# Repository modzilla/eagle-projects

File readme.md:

# My Eagle Projects

## Attention: Most of them are junk!

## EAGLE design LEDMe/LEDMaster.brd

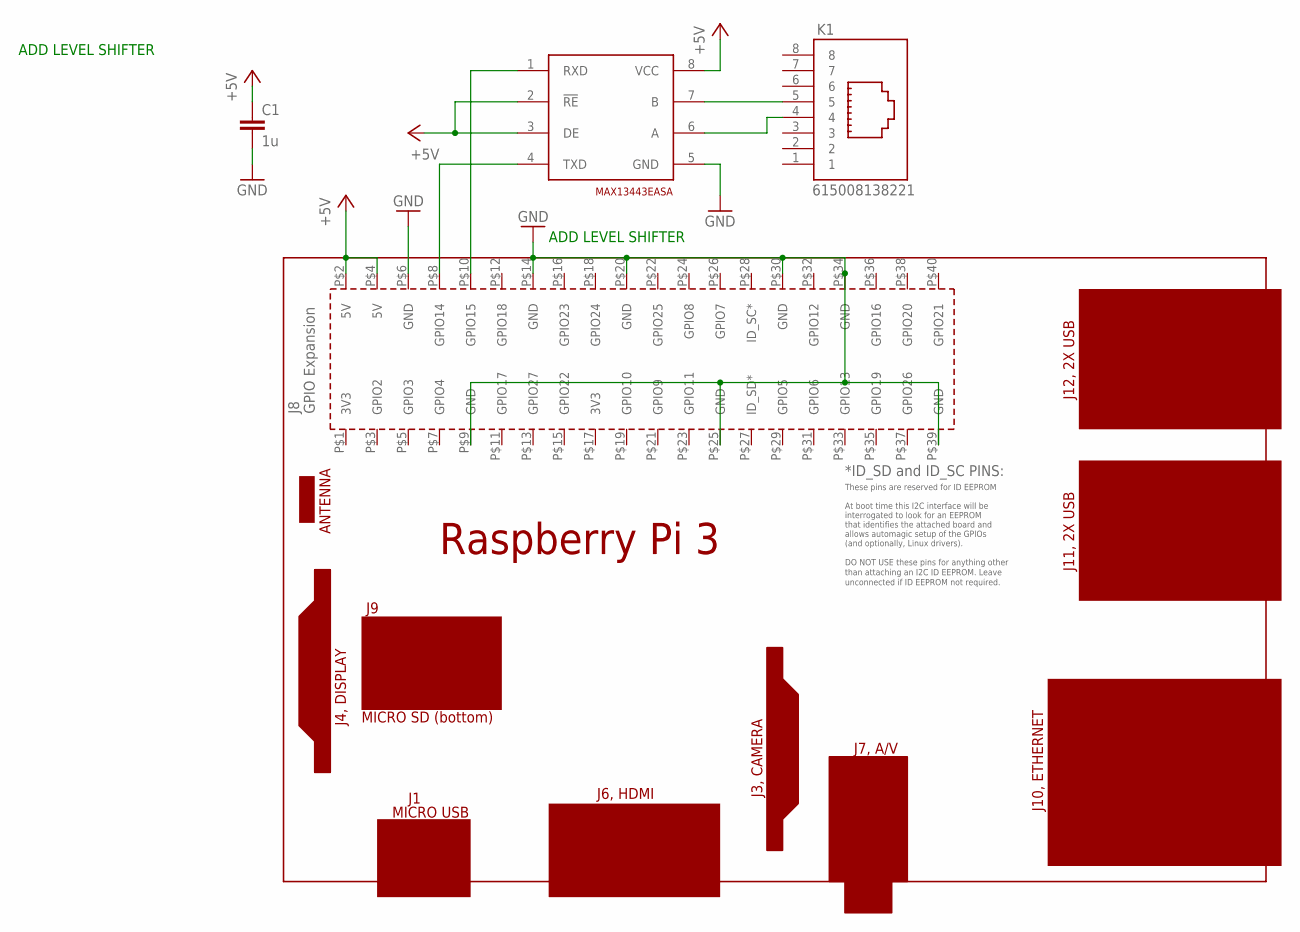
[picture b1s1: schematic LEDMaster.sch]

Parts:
C1: 1u; C1206
K1: 615008138221
PCB1: RPI3
U$1: MAX13443EASA; SO08

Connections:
+5V: C1.1, PCB1.P$2 (5V), PCB1.P$4 (5V), U$1.2 (!RE), U$1.3 (DE), U$1.8 (VCC)
GND: C1.2, PCB1.P$6 (GND), PCB1.P$9 (GND), PCB1.P$14 (GND), PCB1.P$20 (GND), PCB1.P$25 (GND), PCB1.P$30 (GND), PCB1.P$34 (GND), PCB1.P$39 (GND), U$1.5 (GND)
unnamed: PCB1.P$8 (GPIO14), U$1.4 (TXD)
unnamed: PCB1.P$10 (GPIO15), U$1.1 (RXD)
unnamed: K1.5, U$1.7 (B)
unnamed: K1.4, U$1.6 (A)

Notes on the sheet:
ADD LEVEL SHIFTER

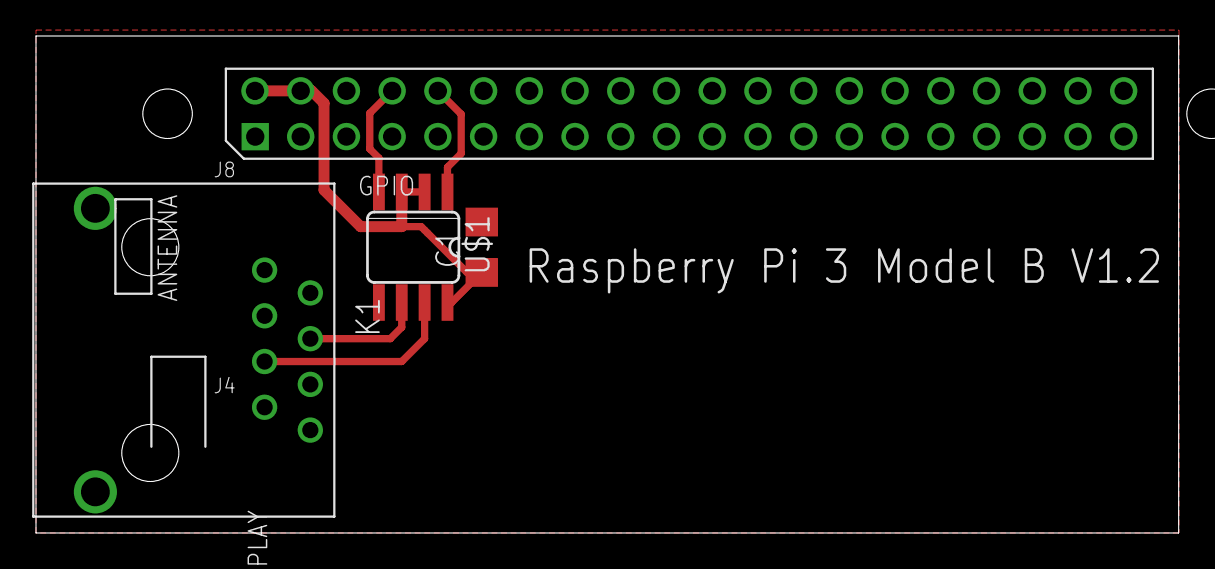
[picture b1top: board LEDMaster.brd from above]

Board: 2 copper layers, 63.5 x 27.6 mm, 4 parts (0 on the bottom side), 6 nets.

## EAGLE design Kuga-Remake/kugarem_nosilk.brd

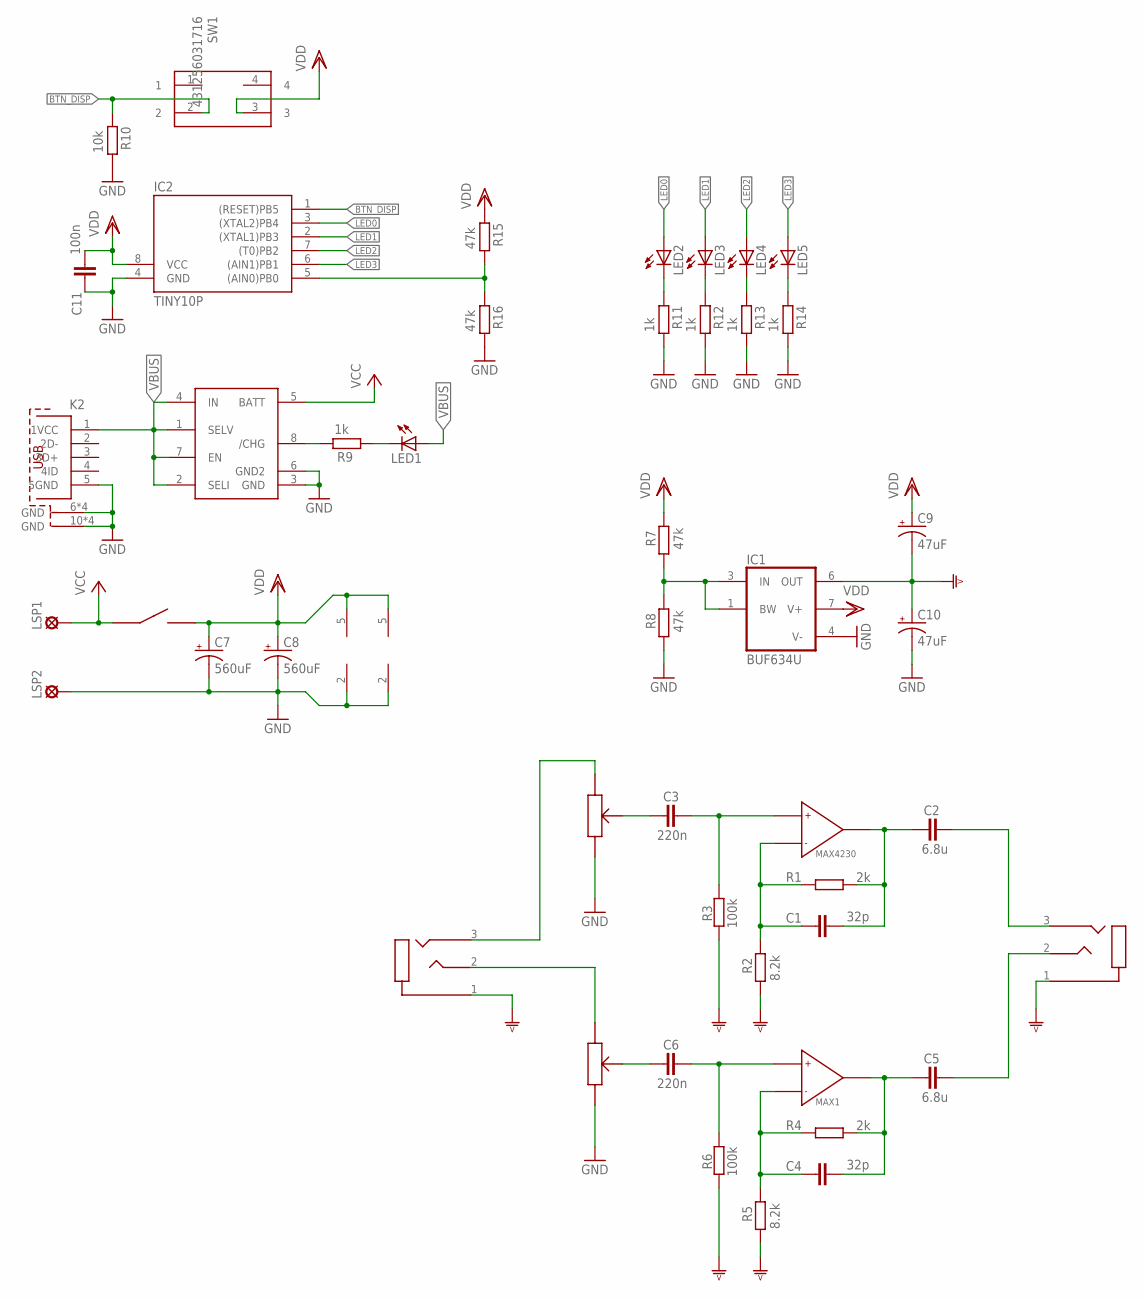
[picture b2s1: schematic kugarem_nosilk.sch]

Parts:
C1, C4: 32p; C1206
C2, C5: 6.8u; C1206
C3, C6: 220n; C1206
C7, C8: 560uF; PANASONIC_G
C9, C10: 47uF; PANASONIC_D
C11: 100n; C1206
IC1: BUF634U; SO08
IC2: TINY10P; DIL08
K2: 629105150921
LED1, LED2, LED3, LED4, LED5: LEDCHIPLED_1206; CHIPLED_1206
LSP1, LSP2: LSP10
MAX1, MAX4230: MAX4230; SOT23-5L
R1, R4: 2k; R1206
R2, R5: 8.2k; R1206
R3, R6: 100k; R1206
R7, R8, R15, R16: 47k; R1206
R9, R11, R12, R13, R14: 1k; R1206
R10: 10k; R1206
SW1: 431256031716
U$1: 100k; PTR902
U$2, U$3: SJ1-3515-SMT-TR; STX-35332-3N-TR
U$4: MAX1811SO8; SO08

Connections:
BTN_DISP: IC2.1 ((RESET)PB5), R10.2, SW1.2
GND: C7.-, C8.-, C10.-, C11.1, IC1.4 (V-), IC2.4 (GND), K2.5 (5GND), K2.6 (GND), K2.7 (GND), K2.8 (GND), K2.9 (GND), K2.10 (GND), K2.11 (GND), K2.12 (GND), K2.13 (GND), LSP2.MP, MAX1.2 (N), MAX4230.2 (N), R8.2, R10.1, R11.1, R12.1, R13.1, R14.1, R16.1, U$1.R13 (13), U$1.R23 (13), U$4.3 (GND), U$4.6 (GND2)
LED0: IC2.3 ((XTAL2)PB4), LED2.A
LED1: IC2.2 ((XTAL1)PB3), LED3.A
LED2: IC2.7 ((T0)PB2), LED4.A
LED3: IC2.6 ((AIN1)PB1), LED5.A
unnamed: C1.2, C2.1, MAX4230.4 (OUT), R1.1
unnamed: C1.1, MAX4230.3 (IN-), R1.2, R2.1
unnamed: C2.2, U$3.3 (RING)
unnamed: C3.2, MAX4230.1 (IN+), R3.1
unnamed: C4.2, C5.1, MAX1.4 (OUT), R4.1
unnamed: C4.1, MAX1.3 (IN-), R4.2, R5.1
unnamed: C3.1, U$1.R22 (12)
unnamed: C6.2, MAX1.1 (IN+), R6.1
unnamed: C5.2, U$3.2 (TIP)
unnamed: C6.1, U$1.R12 (12)
unnamed: U$1.R21 (11), U$2.3 (RING)
unnamed: U$1.R11 (11), U$2.2 (TIP)
unnamed: LED2.C, R11.2
unnamed: LED3.C, R12.2
unnamed: LED1.C, R9.2
unnamed: R9.1, U$4.8 (/CHG)
unnamed: IC1.1 (BW), IC1.3 (IN), R7.2, R8.1
unnamed: LED4.C, R13.2
unnamed: LED5.C, R14.2
unnamed: IC2.5 ((AIN0)PB0), R15.1, R16.2
VBUS: K2.1 (1VCC), LED1.A, U$4.1 (SELV), U$4.2 (SELI), U$4.4 (IN), U$4.7 (EN)
VCC: LSP1.MP, U$1.SW1 (11), U$4.5 (BATT)
VDD: C7.+, C8.+, C9.+, C11.2, IC1.7 (V+), IC2.8 (VCC), MAX1.5, MAX4230.5, R7.1, R15.2, SW1.3, U$1.SW2 (12)
VGND: C9.-, C10.+, IC1.6 (OUT), R2.2, R3.2, R5.2, R6.2, U$2.1 (SLEEVE), U$3.1 (SLEEVE)

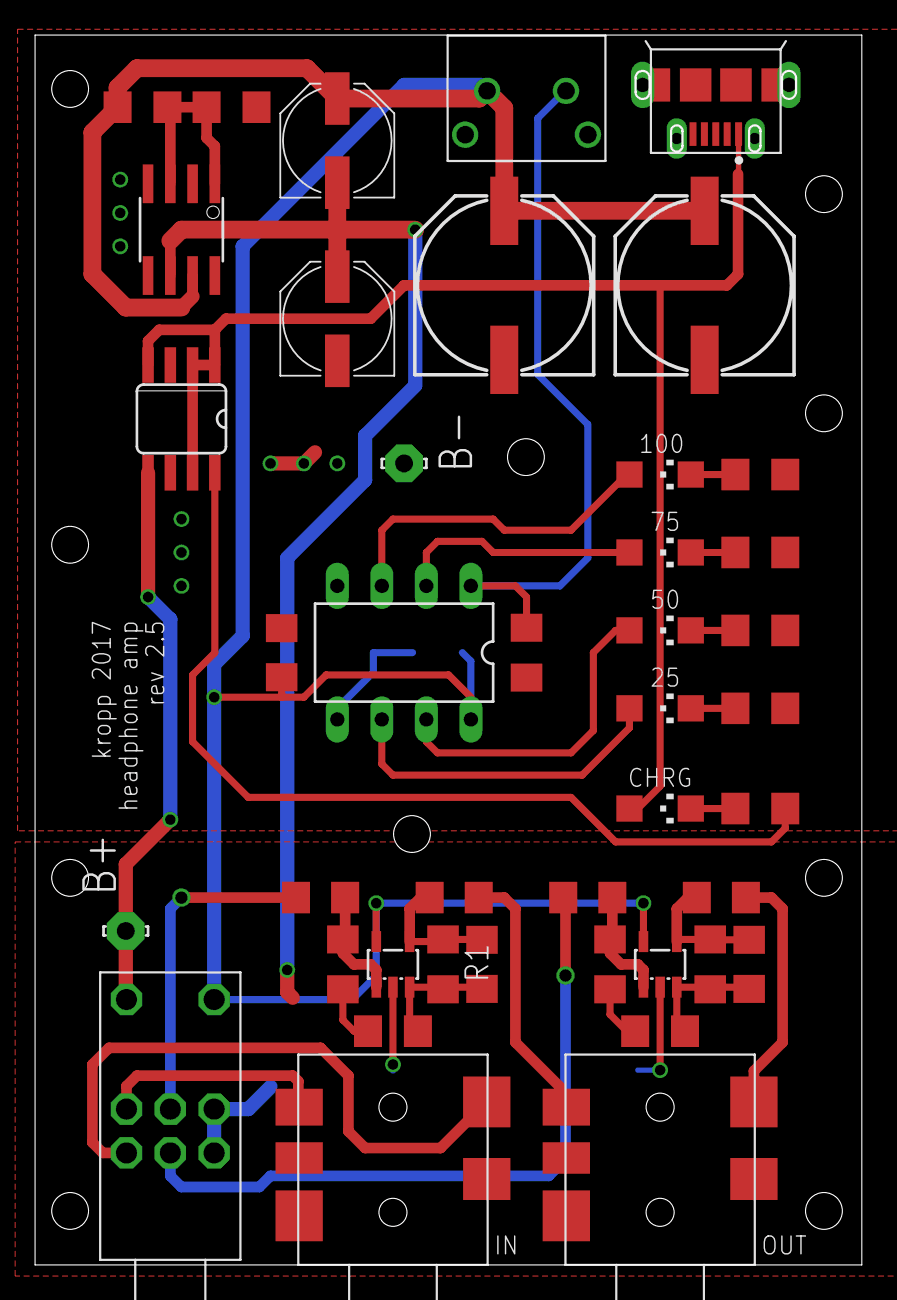
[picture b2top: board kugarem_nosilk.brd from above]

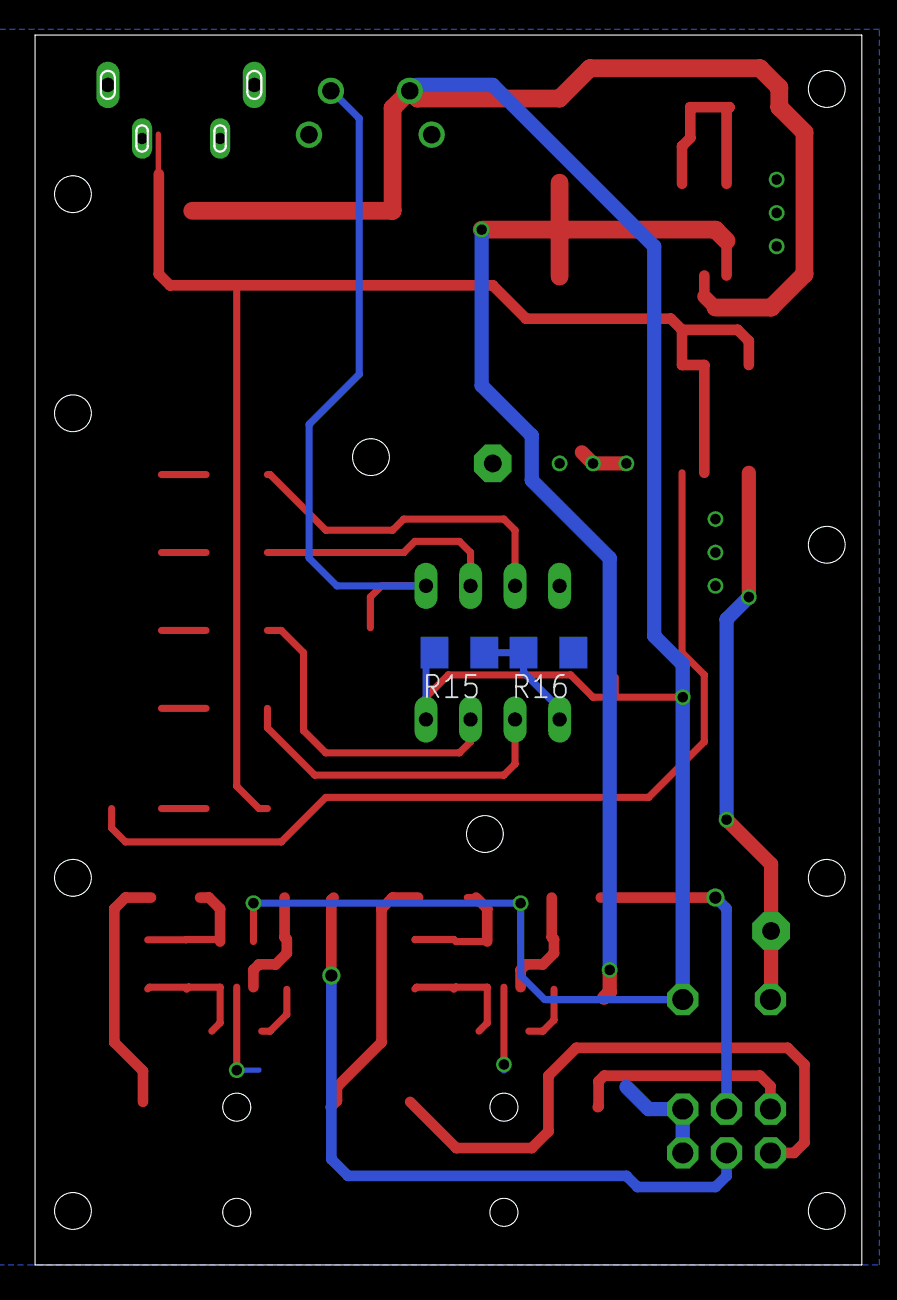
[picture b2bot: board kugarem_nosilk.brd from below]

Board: 2 copper layers, 47.2 x 70.2 mm, 44 parts (2 on the bottom side), 30 nets.

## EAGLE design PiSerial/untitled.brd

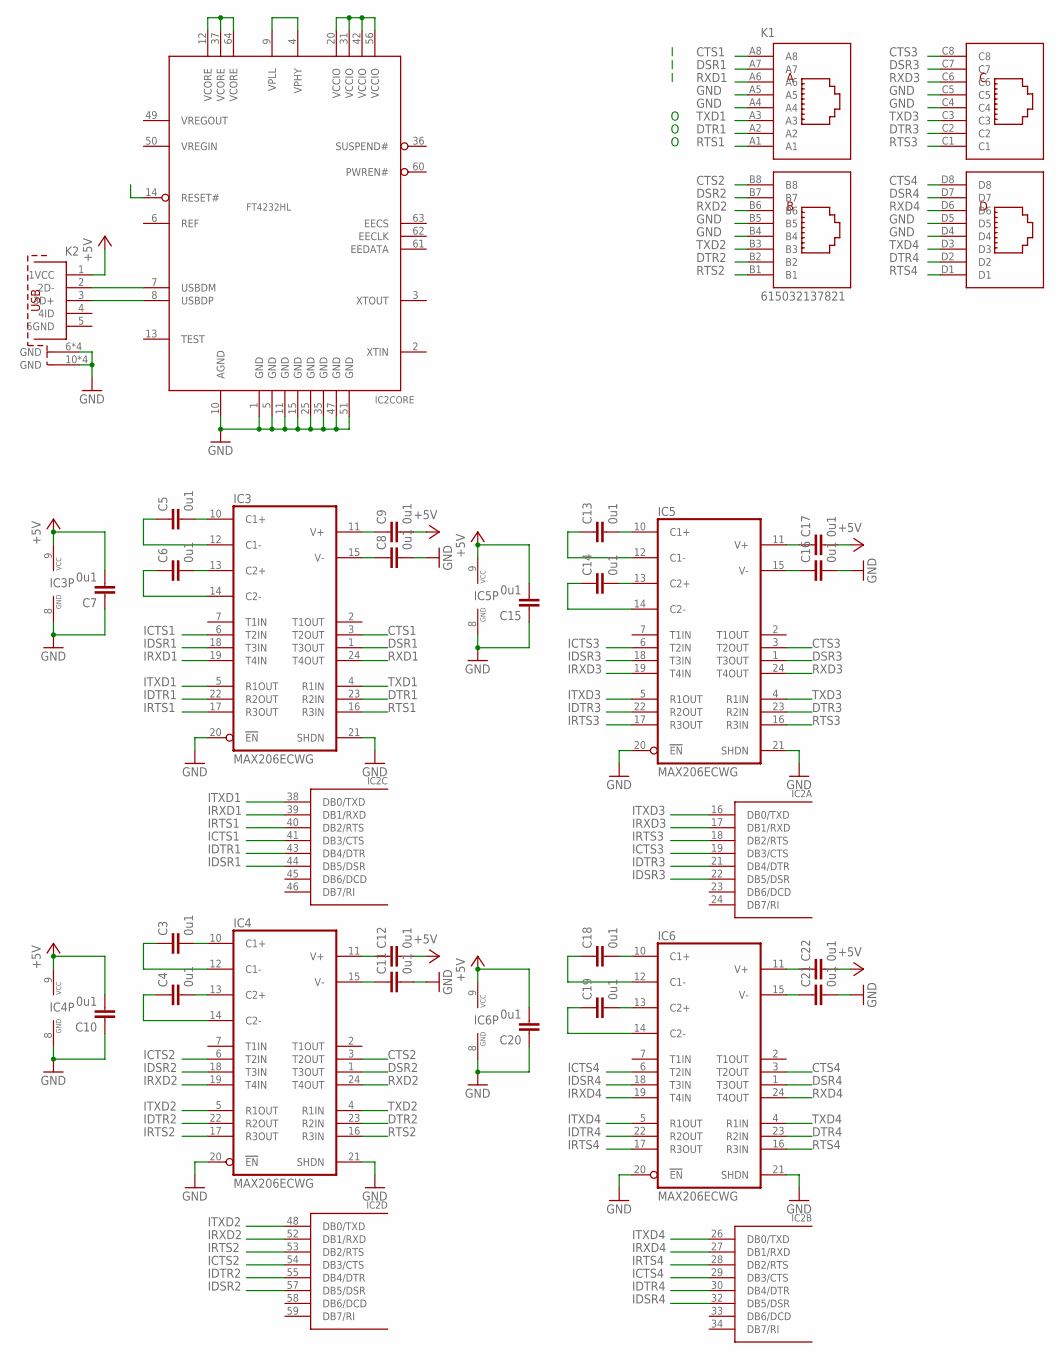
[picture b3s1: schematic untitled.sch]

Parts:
C3, C4, C5, C6, C7, C8, C9, C10, C11, C12, C13, C14, C15, C16, C17, C18, C19, C20, C21, C22: 0u1; C0603
IC2: FT4232HL; LQFP64
IC3, IC4, IC5, IC6: MAX206ECWG; SO24L
K1: 615032137821
K2: 629105150921

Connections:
+5V: C7.2, C9.2, C10.2, C12.2, C15.2, C17.2, C20.2, C22.2, IC3.9 (VCC), IC4.9 (VCC), IC5.9 (VCC), IC6.9 (VCC), K2.1 (1VCC)
CTS1: IC3.3 (T2OUT), K1.A8
CTS2: IC4.3 (T2OUT), K1.B8
CTS3: IC5.3 (T2OUT), K1.C8
CTS4: IC6.3 (T2OUT), K1.D8
DSR1: IC3.1 (T3OUT), K1.A7
DSR2: IC4.1 (T3OUT), K1.B7
DSR3: IC5.1 (T3OUT), K1.C7
DSR4: IC6.1 (T3OUT), K1.D7
DTR1: IC3.23 (R2IN), K1.A2
DTR2: IC4.23 (R2IN), K1.B2
DTR3: IC5.23 (R2IN), K1.C2
DTR4: IC6.23 (R2IN), K1.D2
GND: C7.1, C8.2, C10.1, C11.2, C15.1, C16.2, C20.1, C21.2, IC2.1 (GND), IC2.5 (GND), IC2.10 (AGND), IC2.11 (GND), IC2.15 (GND), IC2.25 (GND), IC2.35 (GND), IC2.47 (GND), IC2.51 (GND), IC3.8 (GND), IC3.20 (EN), IC3.21 (SHDN), IC4.8 (GND), IC4.20 (EN), IC4.21 (SHDN), IC5.8 (GND), IC5.20 (EN), IC5.21 (SHDN), IC6.8 (GND), IC6.20 (EN), IC6.21 (SHDN), K1.A4, K1.A5, K1.B4, K1.B5, K1.C4, K1.C5, K1.D4, K1.D5, K2.6 (GND), K2.7 (GND), K2.8 (GND), K2.9 (GND), K2.10 (GND), K2.11 (GND), K2.12 (GND), K2.13 (GND)
ICTS1: IC2.41 (DB3/CTS), IC3.6 (T2IN)
ICTS2: IC2.54 (DB3/CTS), IC4.6 (T2IN)
ICTS3: IC2.19 (DB3/CTS), IC5.6 (T2IN)
ICTS4: IC2.29 (DB3/CTS), IC6.6 (T2IN)
IDSR1: IC2.44 (DB5/DSR), IC3.18 (T3IN)
IDSR2: IC2.57 (DB5/DSR), IC4.18 (T3IN)
IDSR3: IC2.22 (DB5/DSR), IC5.18 (T3IN)
IDSR4: IC2.32 (DB5/DSR), IC6.18 (T3IN)
IDTR1: IC2.43 (DB4/DTR), IC3.22 (R2OUT)
IDTR2: IC2.55 (DB4/DTR), IC4.22 (R2OUT)
IDTR3: IC2.21 (DB4/DTR), IC5.22 (R2OUT)
IDTR4: IC2.30 (DB4/DTR), IC6.22 (R2OUT)
IRTS1: IC2.40 (DB2/RTS), IC3.17 (R3OUT)
IRTS2: IC2.53 (DB2/RTS), IC4.17 (R3OUT)
IRTS3: IC2.18 (DB2/RTS), IC5.17 (R3OUT)
IRTS4: IC2.28 (DB2/RTS), IC6.17 (R3OUT)
IRXD1: IC2.39 (DB1/RXD), IC3.19 (T4IN)
IRXD2: IC2.52 (DB1/RXD), IC4.19 (T4IN)
IRXD3: IC2.17 (DB1/RXD), IC5.19 (T4IN)
IRXD4: IC2.27 (DB1/RXD), IC6.19 (T4IN)
ITXD1: IC2.38 (DB0/TXD), IC3.5 (R1OUT)
ITXD2: IC2.48 (DB0/TXD), IC4.5 (R1OUT)
ITXD3: IC2.16 (DB0/TXD), IC5.5 (R1OUT)
ITXD4: IC2.26 (DB0/TXD), IC6.5 (R1OUT)
unnamed: C3.2, IC4.10 (C1+)
unnamed: C3.1, IC4.12 (C1-)
unnamed: IC2.20 (VCCIO), IC2.31 (VCCIO), IC2.42 (VCCIO), IC2.56 (VCCIO)
unnamed: IC2.4 (VPHY), IC2.9 (VPLL)
unnamed: C4.2, IC4.13 (C2+)
unnamed: C5.2, IC3.10 (C1+)
unnamed: C5.1, IC3.12 (C1-)
unnamed: C6.2, IC3.13 (C2+)
unnamed: C6.1, IC3.14 (C2-)
unnamed: C4.1, IC4.14 (C2-)
unnamed: C12.1, IC4.11 (V+)
unnamed: C9.1, IC3.11 (V+)
unnamed: C8.1, IC3.15 (V-)
unnamed: C11.1, IC4.15 (V-)
unnamed: C13.2, IC5.10 (C1+)
unnamed: C13.1, IC5.12 (C1-)
unnamed: C14.2, IC5.13 (C2+)
unnamed: C14.1, IC5.14 (C2-)
unnamed: C17.1, IC5.11 (V+)
unnamed: C16.1, IC5.15 (V-)
unnamed: C18.2, IC6.10 (C1+)
unnamed: C18.1, IC6.12 (C1-)
unnamed: C19.2, IC6.13 (C2+)
unnamed: C19.1, IC6.14 (C2-)
unnamed: C22.1, IC6.11 (V+)
unnamed: C21.1, IC6.15 (V-)
unnamed: IC2.12 (VCORE), IC2.37 (VCORE), IC2.64 (VCORE)
unnamed: IC2.8 (USBDP), K2.3 (3D+)
unnamed: IC2.7 (USBDM), K2.2 (2D-)
RTS1: IC3.16 (R3IN), K1.A1
RTS2: IC4.16 (R3IN), K1.B1
RTS3: IC5.16 (R3IN), K1.C1
RTS4: IC6.16 (R3IN), K1.D1
RXD1: IC3.24 (T4OUT), K1.A6
RXD2: IC4.24 (T4OUT), K1.B6
RXD3: IC5.24 (T4OUT), K1.C6
RXD4: IC6.24 (T4OUT), K1.D6
TXD1: IC3.4 (R1IN), K1.A3
TXD2: IC4.4 (R1IN), K1.B3
TXD3: IC5.4 (R1IN), K1.C3
TXD4: IC6.4 (R1IN), K1.D3

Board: 2 copper layers, 27 parts (0 on the bottom side), 79 nets, no tracks yet.

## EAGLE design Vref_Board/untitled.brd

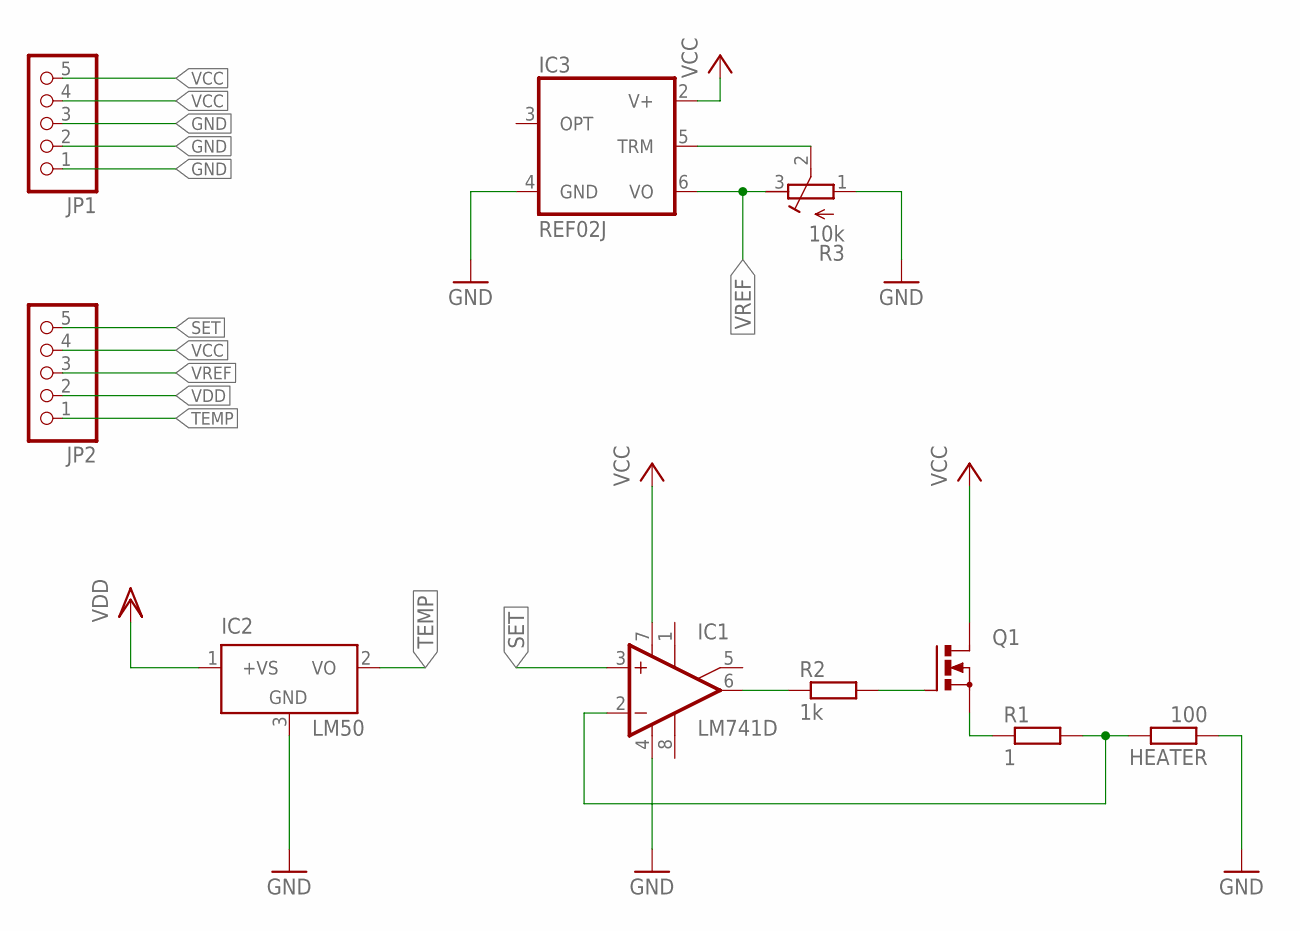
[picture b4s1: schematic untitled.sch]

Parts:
HEATER: 100; WSC0001
IC1: LM741D; SO08
IC2: LM50; SOT23
IC3: REF02J; TO99
JP1, JP2: PINHD-1X5; 1X05
Q1: N-MOSFET-SO8S; SO-08
R1: 1; R1206
R2: 1k; R1206
R3: 10k; RTRIM3103

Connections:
GND: HEATER.1, IC1.4 (V-), IC2.3 (GND), IC3.4 (GND), JP1.1, JP1.2, JP1.3, R3.1 (A)
unnamed: IC1.6 (OUT), R2.1
unnamed: Q1.4 (G), R2.2
unnamed: HEATER.2, IC1.2 (-IN), R1.2
unnamed: Q1.1 (S), Q1.2 (S), Q1.3 (S), R1.1
unnamed: IC3.5 (TRM), R3.2 (S)
SET: IC1.3 (+IN), JP2.5
TEMP: IC2.2 (VO), JP2.1
VCC: IC1.7 (V+), IC3.2 (V+), JP1.4, JP1.5, JP2.4, Q1.5 (D), Q1.6 (D), Q1.7 (D), Q1.8 (D)
VDD: IC2.1 (+VS), JP2.2
VREF: IC3.6 (VO), JP2.3, R3.3 (E)

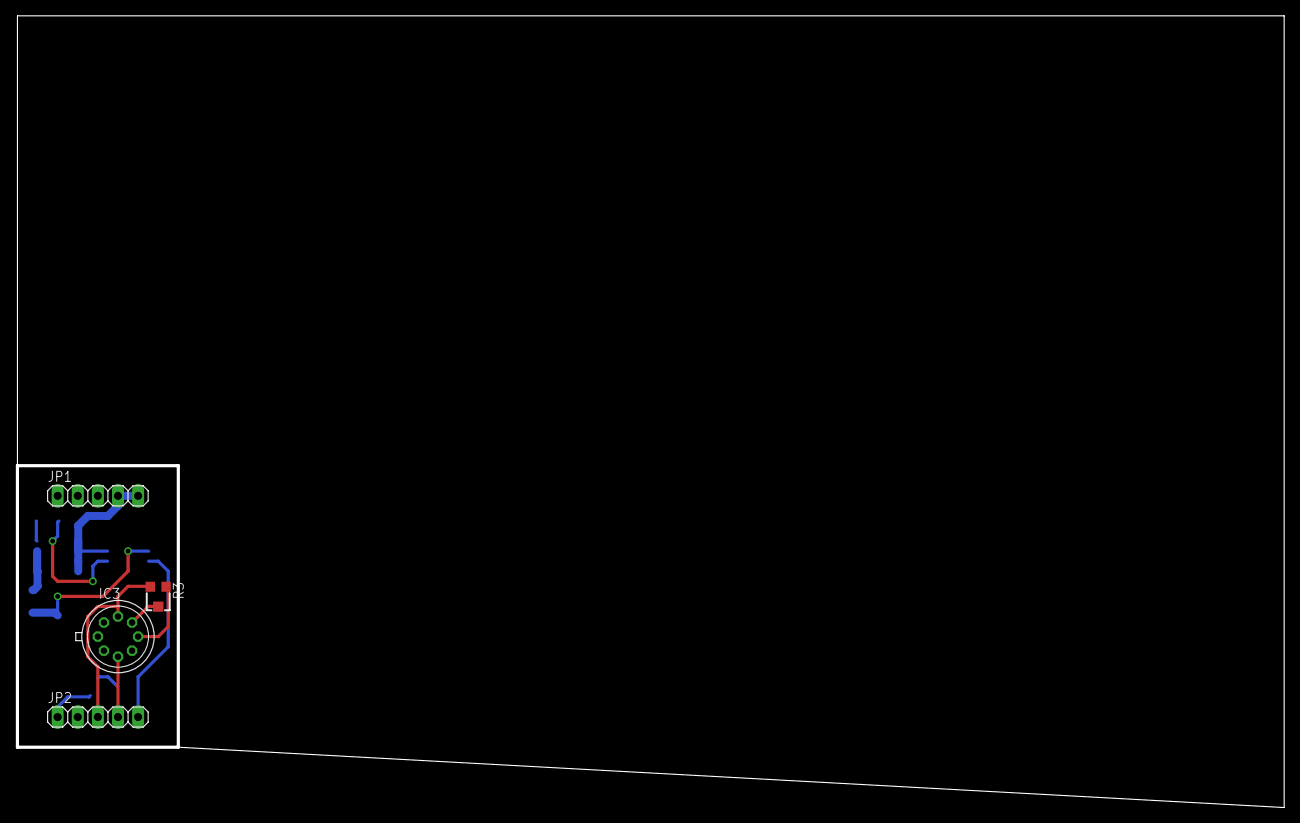
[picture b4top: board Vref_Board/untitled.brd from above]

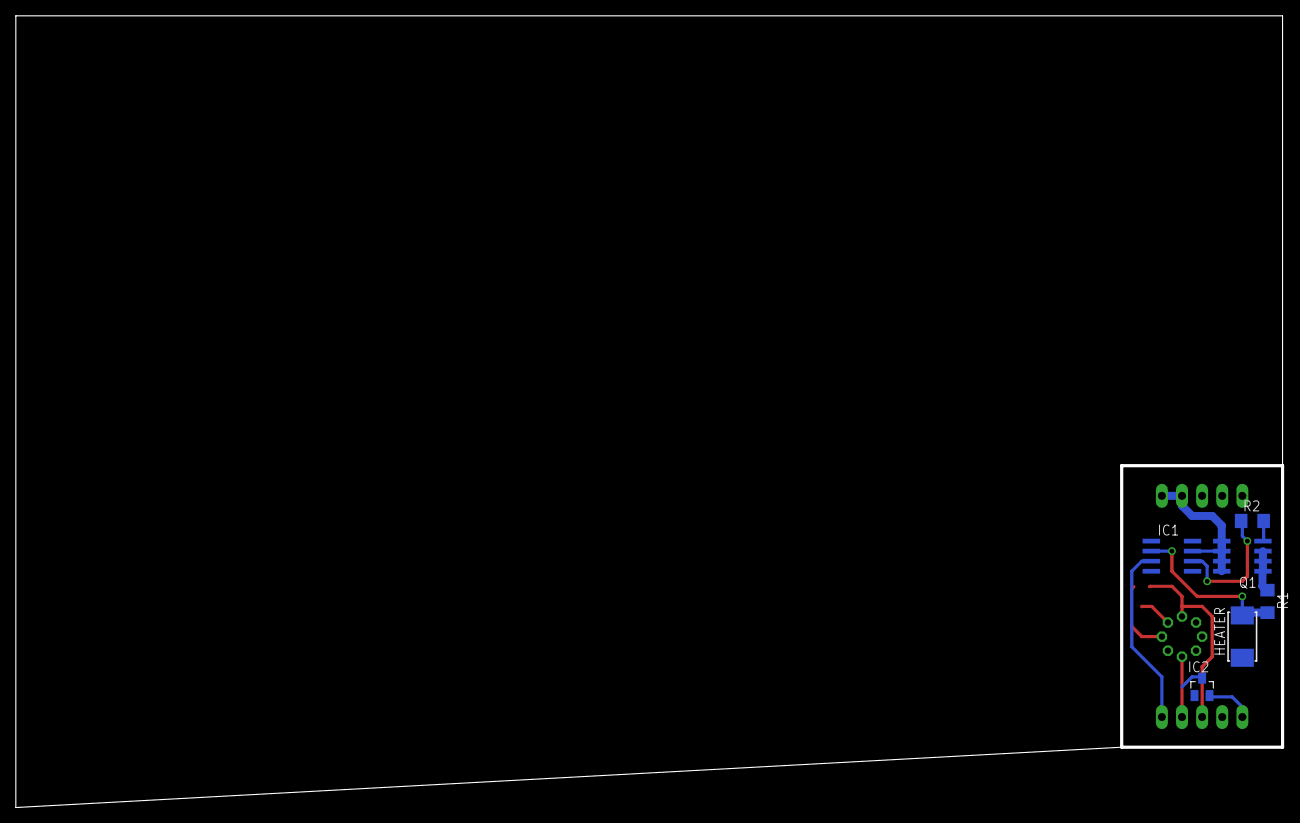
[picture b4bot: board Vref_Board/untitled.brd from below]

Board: 2 copper layers, 160.0 x 100.0 mm, 10 parts (6 on the bottom side), 11 nets.

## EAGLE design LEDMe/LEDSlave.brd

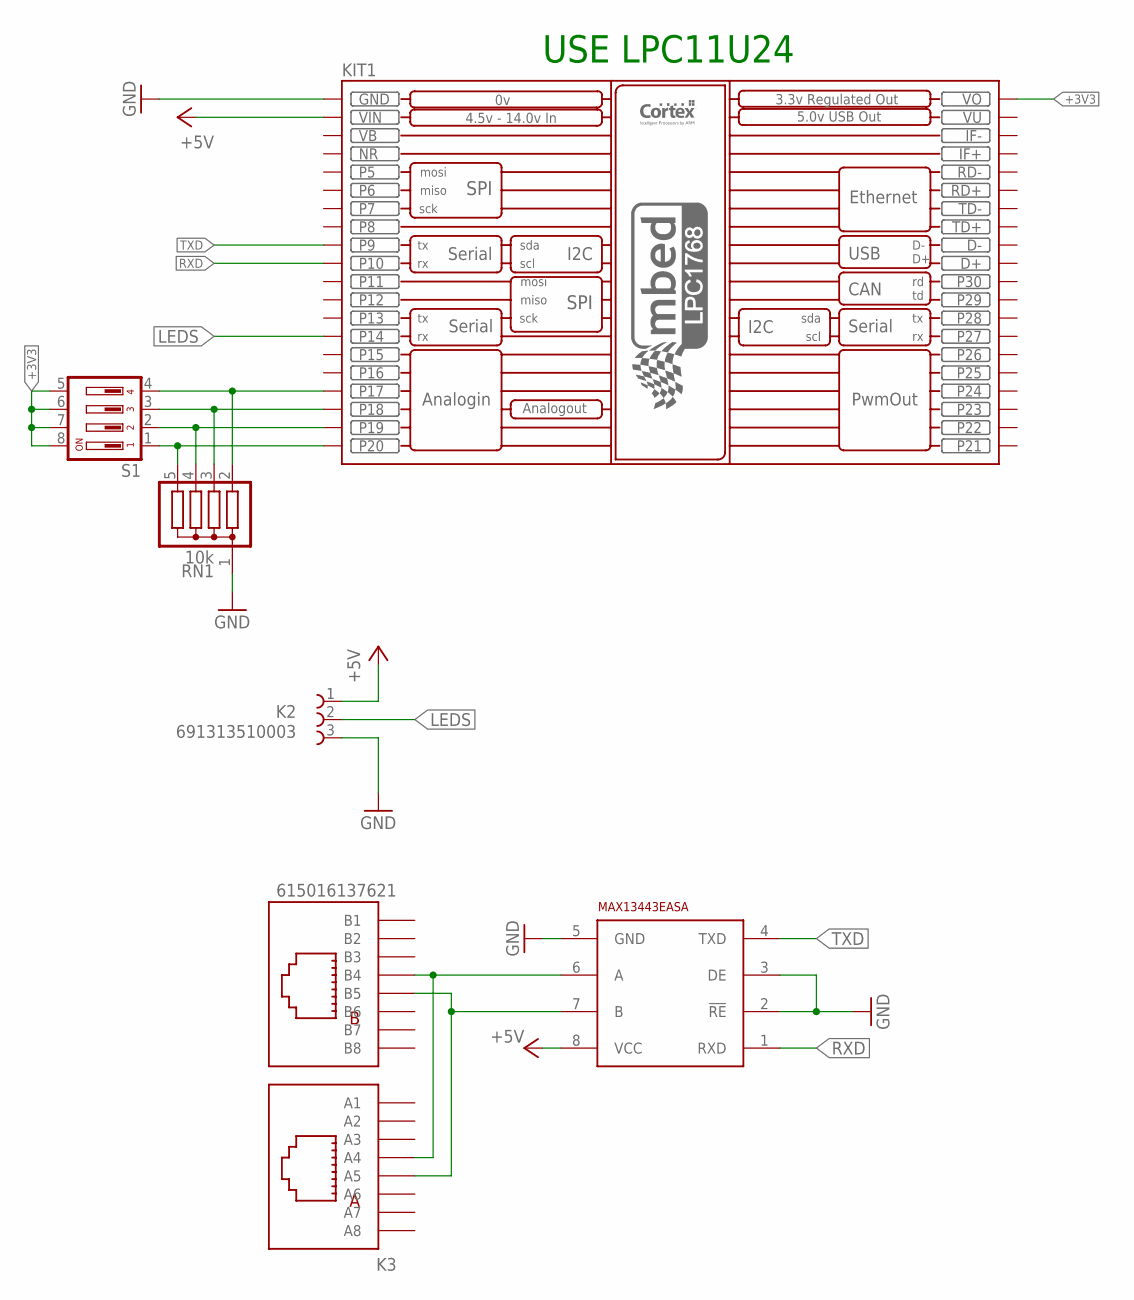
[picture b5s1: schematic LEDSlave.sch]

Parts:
K2: 691313510003
K3: 615016137621
KIT1: MBED_NXP_LPC1768; MBED-KIT
RN1: 10k; SIL5
S1: DA04; DA-04
U$1: MAX13443EASA; SO08

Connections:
+3V3: KIT1.VOUT (VO), S1.5, S1.6, S1.7, S1.8
+5V: K2.1, KIT1.VIN, U$1.8 (VCC)
GND: K2.3, KIT1.GND, RN1.1, U$1.2 (!RE), U$1.3 (DE), U$1.5 (GND)
LEDS: K2.2, KIT1.P$14 (P14)
unnamed: KIT1.P$20 (P20), RN1.5, S1.1
unnamed: KIT1.P$19 (P19), RN1.4, S1.2
unnamed: KIT1.P$18 (P18), RN1.3, S1.3
unnamed: KIT1.P$17 (P17), RN1.2, S1.4
unnamed: K3.A4, K3.B4, U$1.6 (A)
unnamed: K3.A5, K3.B5, U$1.7 (B)
NR: KIT1.NR
RXD: KIT1.P$10 (P10), U$1.1 (RXD)
TXD: KIT1.P$9 (P9), U$1.4 (TXD)
VB: KIT1.VB
VU: KIT1.VU

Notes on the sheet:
USE LPC11U24

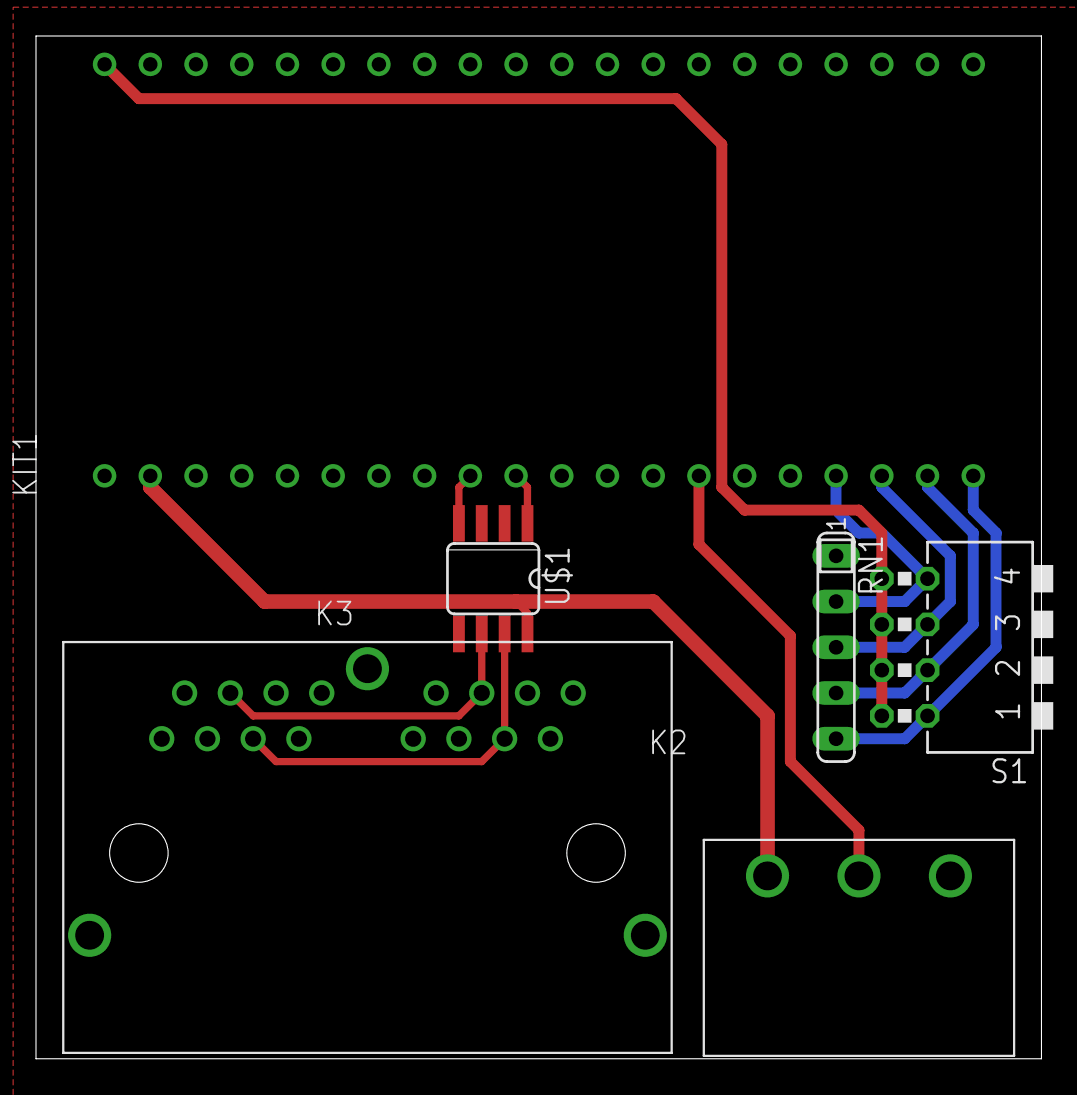
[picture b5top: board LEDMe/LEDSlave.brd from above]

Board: 2 copper layers, 55.9 x 56.8 mm, 6 parts (0 on the bottom side), 12 nets.

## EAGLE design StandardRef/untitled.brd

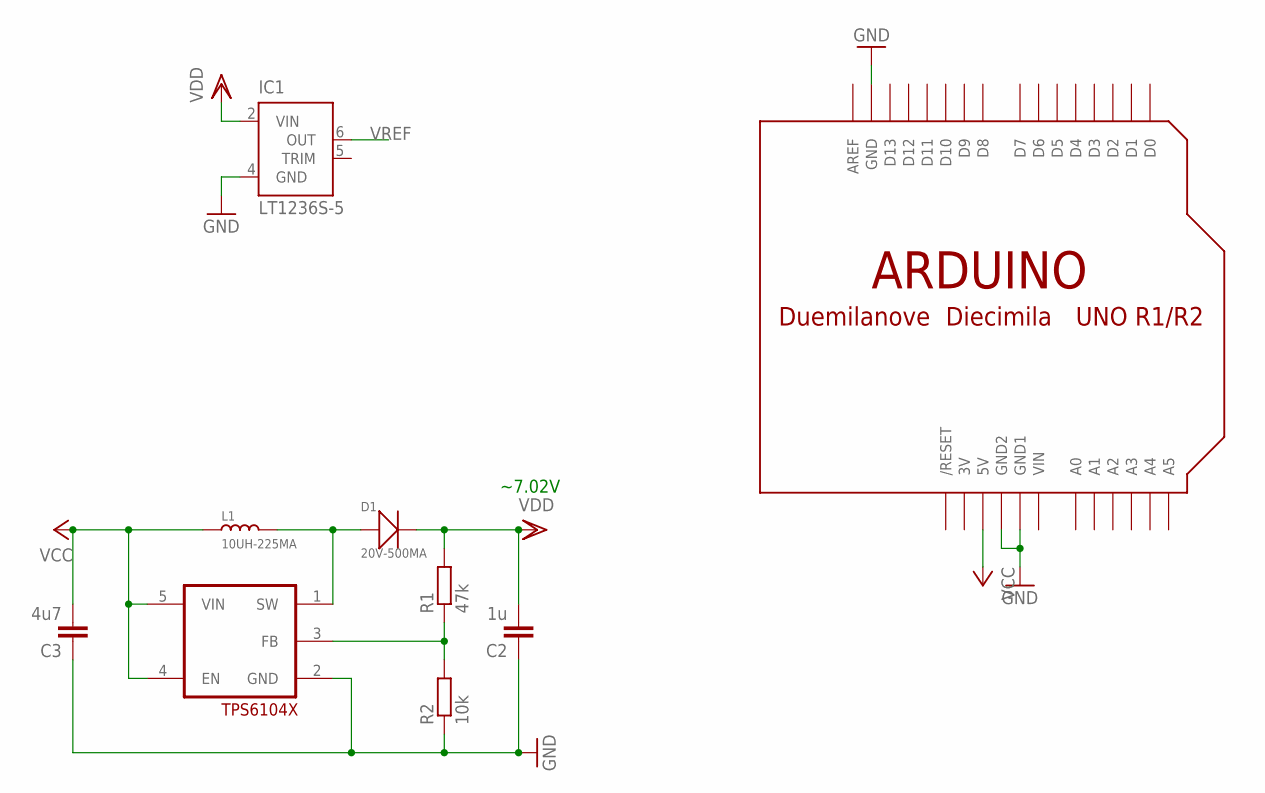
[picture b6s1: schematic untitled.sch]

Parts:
C2: 1u; C1206
C3: 4u7; C1206
D1: 20V-500MA; SOD-123
IC1: LT1236S-5; SOIC8
L1: 10UH-225MA; L0806
R1: 47k; R0805
R2: 10k; R0805
U$1: ARDUINO-NOHOLE
U$2: TPS6104X; SOT23-DBV

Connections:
3V: U$1.3V
GND: C2.1, C3.1, IC1.4 (GND), R2.1, U$1.GND, U$1.GND1, U$1.GND2, U$2.2 (GND)
unnamed: D1.+, L1.2, U$2.1 (SW)
unnamed: R1.1, R2.2, U$2.3 (FB)
VCC: C3.2, L1.1, U$1.5V, U$2.4 (EN), U$2.5 (VIN)
VDD: C2.2, D1.-, IC1.2 (VIN), R1.2
VIN: U$1.VIN
VREF: IC1.6 (OUT)

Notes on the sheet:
~7.02V

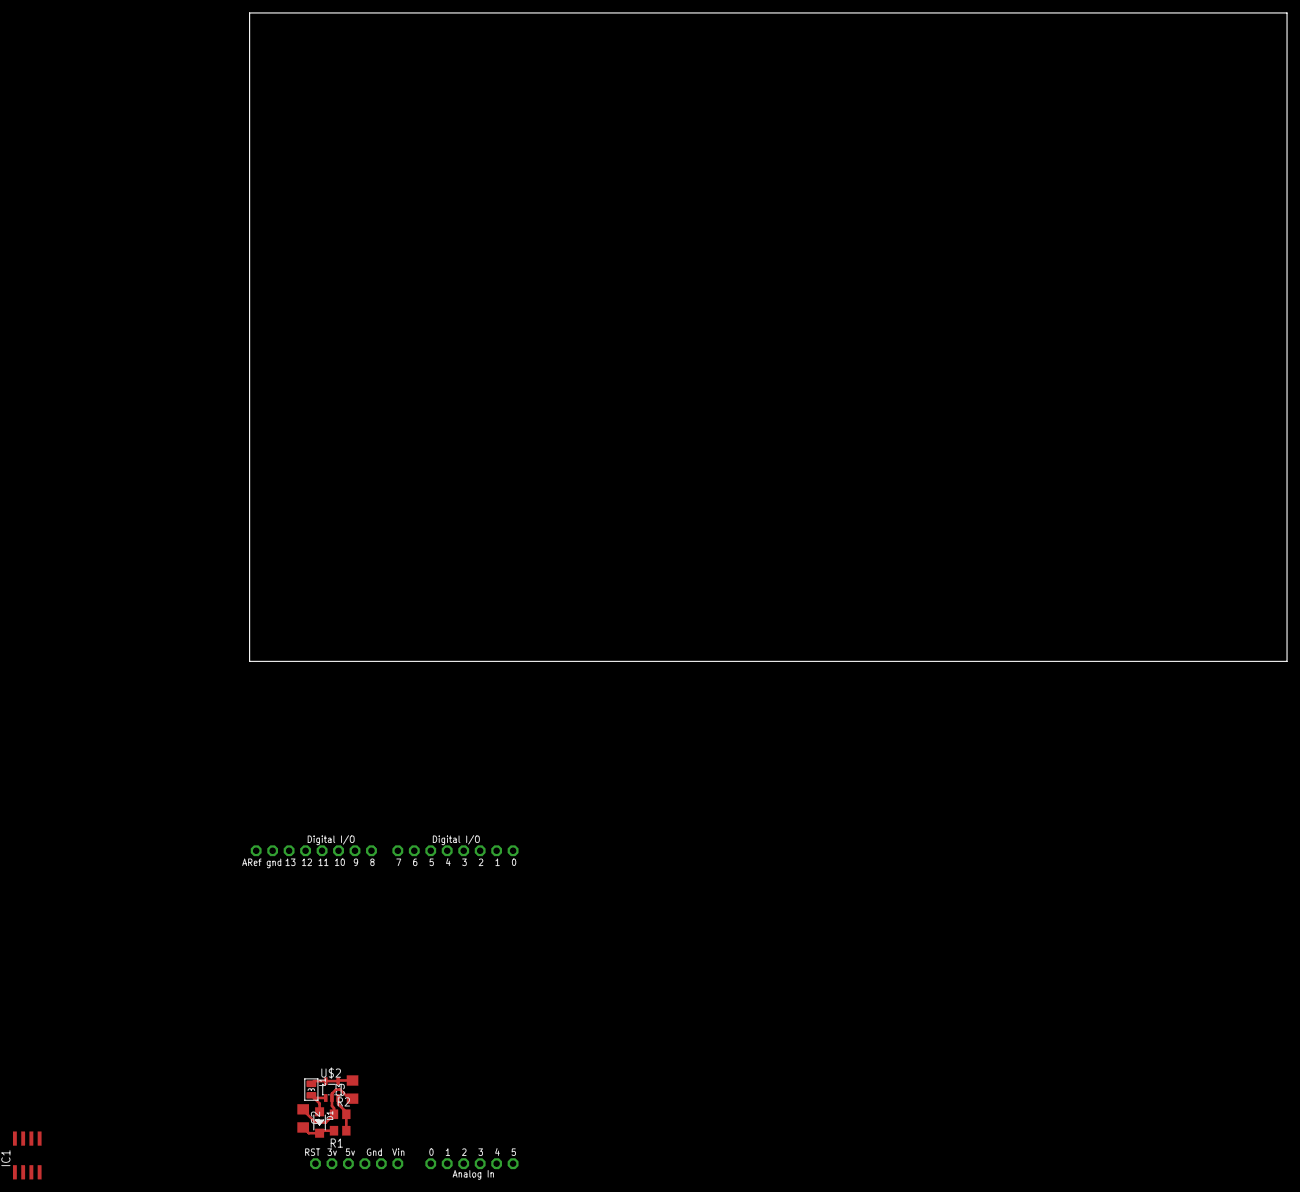
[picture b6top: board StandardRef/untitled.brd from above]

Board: 2 copper layers, 160.0 x 100.0 mm, 9 parts (0 on the bottom side), 5 nets.

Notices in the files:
parts and their libraries:
Wire_to_Board_Connectors_rev15d: Copyright: Würth Elektronik
SparkFun-Capacitors: Licensing: Creative Commons ShareAlike 4.0 International - https://creativecommons.org/licenses/by-sa/4.0
